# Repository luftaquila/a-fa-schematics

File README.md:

# E-Formula 전기시스템 파트 회로도 / PCB / 배선

상위 프로젝트: [luftaquila/a-fa-landing](https://github.com/luftaquila/a-fa-landing)

* 회로도  
    * *EV.kicad_pro*  
       * KiCAD 6.0 프로젝트  
       * 메인 회로도입니다. 추상적으로 차량의 모든 고전압/저전압 전기 계통이 표현되어 있습니다. 메인 회로도 하위의 계층 회로도는 개별 구성 요소를 추상화합니다. 계층 회로도 중 `/PCB` 폴더 하위의 파일들은 실제 PCB의 회로도입니다.

* PCB  
    * */PCB/\*.kicad_pcb*  
       * KiCAD 6.0 PCB 아트워크  
       * 각 PCB 폴더는 하나의 독립적인 KiCAD 프로젝트입니다. 메인 회로도인 `EV.kicad_sch` 파일이 계층 회로 구성을 통해 각 PCB 폴더의 `*.kicad_sch` 파일을 가리키는 방식으로 서로 연결되어 있습니다.

* 배선  
    * *wirings*
       * 차량의 모든 외부 배선을 표현하는 [WireViz](https://github.com/formatc1702/WireViz) 배선 체계도입니다.

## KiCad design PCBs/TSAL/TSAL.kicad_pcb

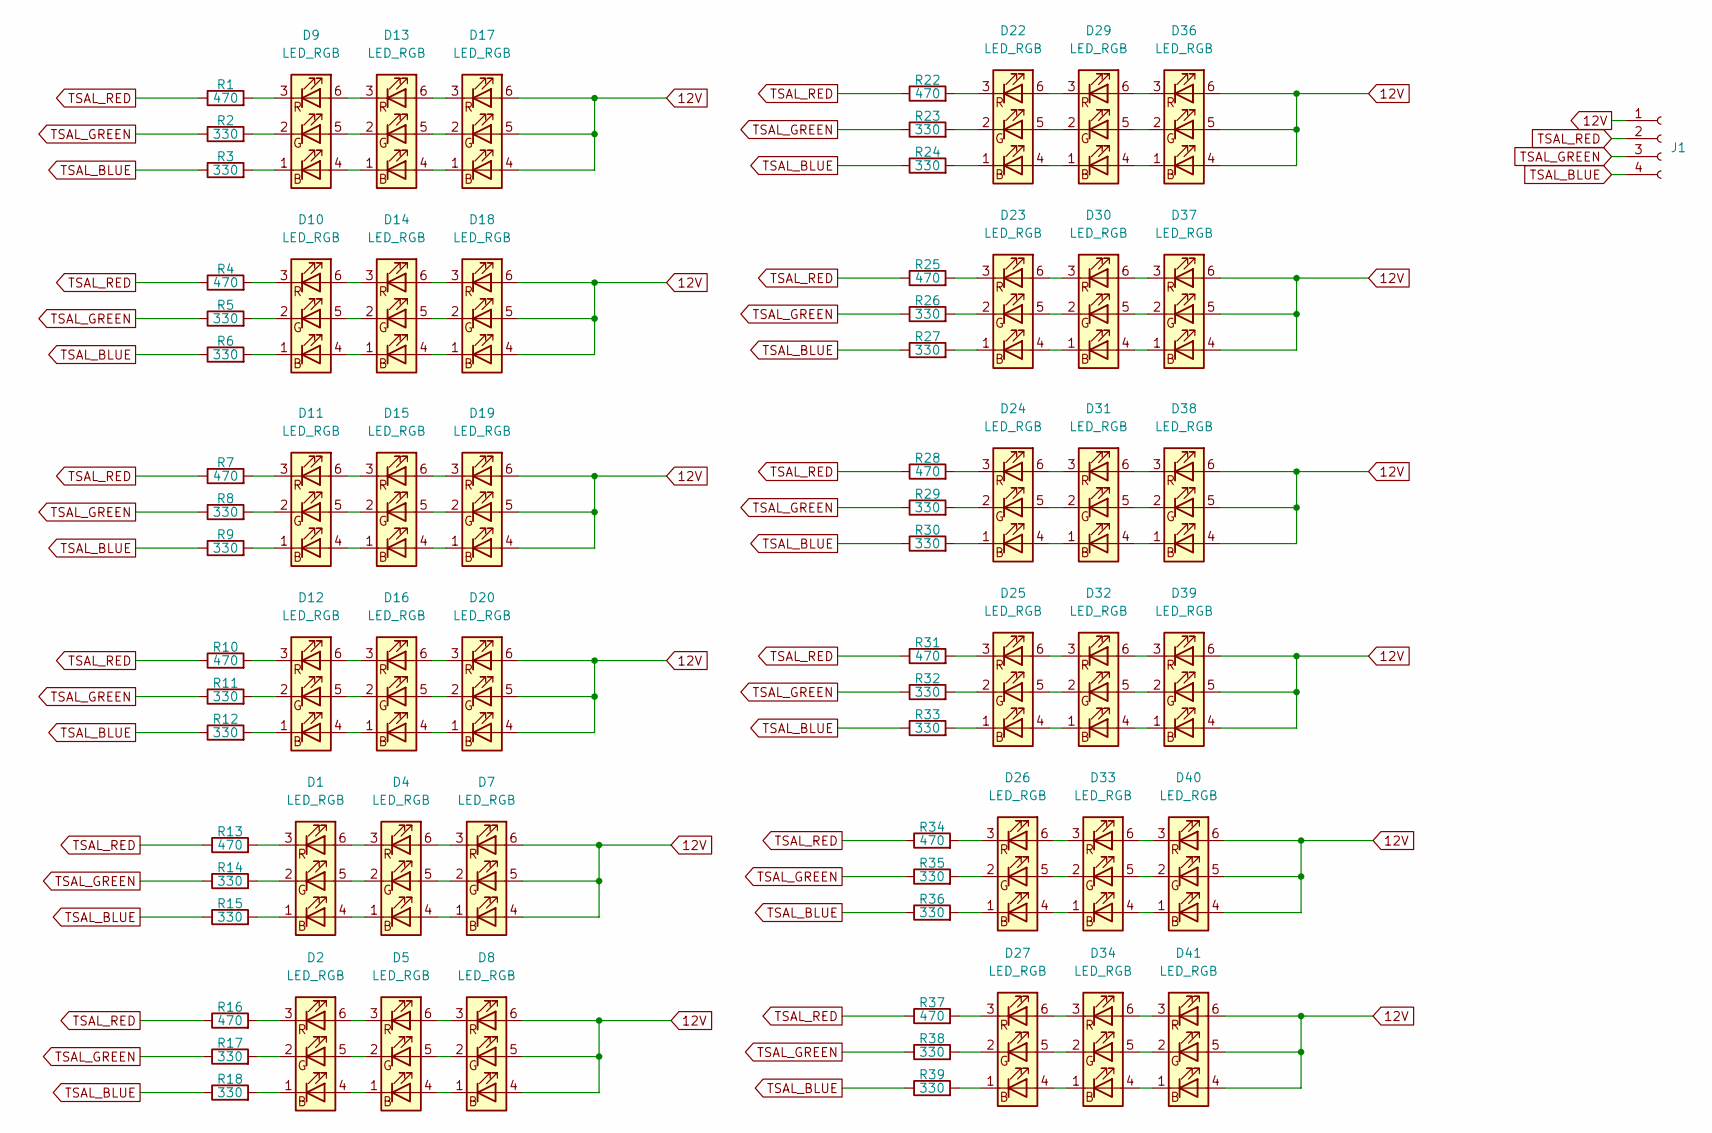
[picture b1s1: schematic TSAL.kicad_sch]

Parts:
D1, D2, D4, D5, D7, D8, D9, D10, D11, D12, D13, D14, D15, D16, D17, D18, D19, D20, D22, D23, D24, D25, D26, D27, D29, D30, D31, D32, D33, D34, D36, D37, D38, D39, D40, D41: LED_RGB; LED_RGB_5050-6
J1: Conn_01x04_Female; PinHeader_1x04_P2.54mm_Vertical
R1, R4, R7, R10, R13, R16, R22, R25, R28, R31, R34, R37: 470; R_1206_3216Metric_Pad1.30x1.75mm_HandSolder
R2, R3, R5, R6, R8, R9, R11, R12, R14, R15, R17, R18, R23, R24, R26, R27, R29, R30, R32, R33, R35, R36, R38, R39: 330; R_1206_3216Metric_Pad1.30x1.75mm_HandSolder

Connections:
12V: D7.4 (BA), D7.5 (GA), D7.6 (RA), D8.4 (BA), D8.5 (GA), D8.6 (RA), D17.4 (BA), D17.5 (GA), D17.6 (RA), D18.4 (BA), D18.5 (GA), D18.6 (RA), D19.4 (BA), D19.5 (GA), D19.6 (RA), D20.4 (BA), D20.5 (GA), D20.6 (RA), D36.4 (BA), D36.5 (GA), D36.6 (RA), D37.4 (BA), D37.5 (GA), D37.6 (RA), D38.4 (BA), D38.5 (GA), D38.6 (RA), D39.4 (BA), D39.5 (GA), D39.6 (RA), D40.4 (BA), D40.5 (GA), D40.6 (RA), D41.4 (BA), D41.5 (GA), D41.6 (RA), J1.1
unnamed: D1.1 (BK), R15.2
unnamed: D1.2 (GK), R14.2
unnamed: D1.3 (RK), R13.2
unnamed: D1.4 (BA), D4.1 (BK)
unnamed: D1.5 (GA), D4.2 (GK)
unnamed: D1.6 (RA), D4.3 (RK)
unnamed: D2.1 (BK), R18.2
unnamed: D2.2 (GK), R17.2
unnamed: D2.3 (RK), R16.2
unnamed: D2.4 (BA), D5.1 (BK)
unnamed: D2.5 (GA), D5.2 (GK)
unnamed: D2.6 (RA), D5.3 (RK)
unnamed: D4.4 (BA), D7.1 (BK)
unnamed: D4.5 (GA), D7.2 (GK)
unnamed: D4.6 (RA), D7.3 (RK)
unnamed: D5.4 (BA), D8.1 (BK)
unnamed: D5.5 (GA), D8.2 (GK)
unnamed: D5.6 (RA), D8.3 (RK)
unnamed: D9.1 (BK), R3.2
unnamed: D9.2 (GK), R2.2
unnamed: D9.3 (RK), R1.2
unnamed: D10.1 (BK), R6.2
unnamed: D10.2 (GK), R5.2
unnamed: D10.3 (RK), R4.2
unnamed: D10.4 (BA), D14.1 (BK)
unnamed: D10.5 (GA), D14.2 (GK)
unnamed: D10.6 (RA), D14.3 (RK)
unnamed: D11.1 (BK), R9.2
unnamed: D11.2 (GK), R8.2
unnamed: D11.3 (RK), R7.2
unnamed: D11.4 (BA), D15.1 (BK)
unnamed: D11.5 (GA), D15.2 (GK)
unnamed: D11.6 (RA), D15.3 (RK)
unnamed: D12.1 (BK), R12.2
unnamed: D12.2 (GK), R11.2
unnamed: D12.3 (RK), R10.2
unnamed: D12.4 (BA), D16.1 (BK)
unnamed: D12.5 (GA), D16.2 (GK)
unnamed: D12.6 (RA), D16.3 (RK)
unnamed: D9.4 (BA), D13.1 (BK)
unnamed: D9.5 (GA), D13.2 (GK)
unnamed: D9.6 (RA), D13.3 (RK)
unnamed: D13.4 (BA), D17.1 (BK)
unnamed: D13.5 (GA), D17.2 (GK)
unnamed: D13.6 (RA), D17.3 (RK)
unnamed: D14.4 (BA), D18.1 (BK)
unnamed: D14.5 (GA), D18.2 (GK)
unnamed: D14.6 (RA), D18.3 (RK)
unnamed: D15.4 (BA), D19.1 (BK)
unnamed: D15.5 (GA), D19.2 (GK)
unnamed: D15.6 (RA), D19.3 (RK)
unnamed: D16.4 (BA), D20.1 (BK)
unnamed: D16.5 (GA), D20.2 (GK)
unnamed: D16.6 (RA), D20.3 (RK)
unnamed: D22.1 (BK), R24.2
unnamed: D22.2 (GK), R23.2
unnamed: D22.3 (RK), R22.2
unnamed: D22.4 (BA), D29.1 (BK)
unnamed: D22.5 (GA), D29.2 (GK)
unnamed: D22.6 (RA), D29.3 (RK)
unnamed: D23.1 (BK), R27.2
unnamed: D23.2 (GK), R26.2
unnamed: D23.3 (RK), R25.2
unnamed: D23.4 (BA), D30.1 (BK)
unnamed: D23.5 (GA), D30.2 (GK)
unnamed: D23.6 (RA), D30.3 (RK)
unnamed: D24.1 (BK), R30.2
unnamed: D24.2 (GK), R29.2
unnamed: D24.3 (RK), R28.2
unnamed: D24.4 (BA), D31.1 (BK)
unnamed: D24.5 (GA), D31.2 (GK)
unnamed: D24.6 (RA), D31.3 (RK)
unnamed: D25.1 (BK), R33.2
unnamed: D25.2 (GK), R32.2
unnamed: D25.3 (RK), R31.2
unnamed: D25.4 (BA), D32.1 (BK)
unnamed: D25.5 (GA), D32.2 (GK)
unnamed: D25.6 (RA), D32.3 (RK)
unnamed: D26.1 (BK), R36.2
unnamed: D26.2 (GK), R35.2
unnamed: D26.3 (RK), R34.2
unnamed: D26.4 (BA), D33.1 (BK)
unnamed: D26.5 (GA), D33.2 (GK)
unnamed: D26.6 (RA), D33.3 (RK)
unnamed: D27.1 (BK), R39.2
unnamed: D27.2 (GK), R38.2
unnamed: D27.3 (RK), R37.2
unnamed: D27.4 (BA), D34.1 (BK)
unnamed: D27.5 (GA), D34.2 (GK)
unnamed: D27.6 (RA), D34.3 (RK)
unnamed: D29.4 (BA), D36.1 (BK)
unnamed: D29.5 (GA), D36.2 (GK)
unnamed: D29.6 (RA), D36.3 (RK)
unnamed: D30.4 (BA), D37.1 (BK)
unnamed: D30.5 (GA), D37.2 (GK)
unnamed: D30.6 (RA), D37.3 (RK)
unnamed: D31.4 (BA), D38.1 (BK)
unnamed: D31.5 (GA), D38.2 (GK)
unnamed: D31.6 (RA), D38.3 (RK)
unnamed: D32.4 (BA), D39.1 (BK)
unnamed: D32.5 (GA), D39.2 (GK)
unnamed: D32.6 (RA), D39.3 (RK)
unnamed: D33.4 (BA), D40.1 (BK)
unnamed: D33.5 (GA), D40.2 (GK)
unnamed: D33.6 (RA), D40.3 (RK)
unnamed: D34.4 (BA), D41.1 (BK)
unnamed: D34.5 (GA), D41.2 (GK)
unnamed: D34.6 (RA), D41.3 (RK)
TSAL_BLUE: J1.4, R3.1, R6.1, R9.1, R12.1, R15.1, R18.1, R24.1, R27.1, R30.1, R33.1, R36.1, R39.1
TSAL_GREEN: J1.3, R2.1, R5.1, R8.1, R11.1, R14.1, R17.1, R23.1, R26.1, R29.1, R32.1, R35.1, R38.1
TSAL_RED: J1.2, R1.1, R4.1, R7.1, R10.1, R13.1, R16.1, R22.1, R25.1, R28.1, R31.1, R34.1, R37.1

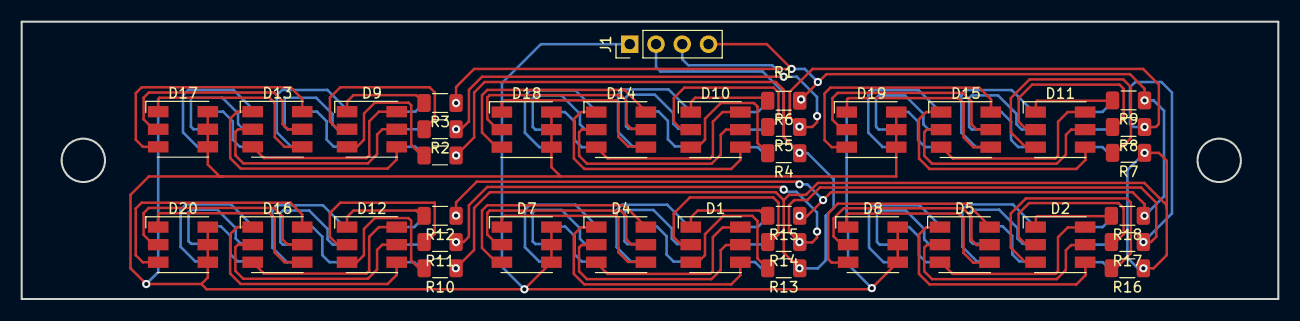
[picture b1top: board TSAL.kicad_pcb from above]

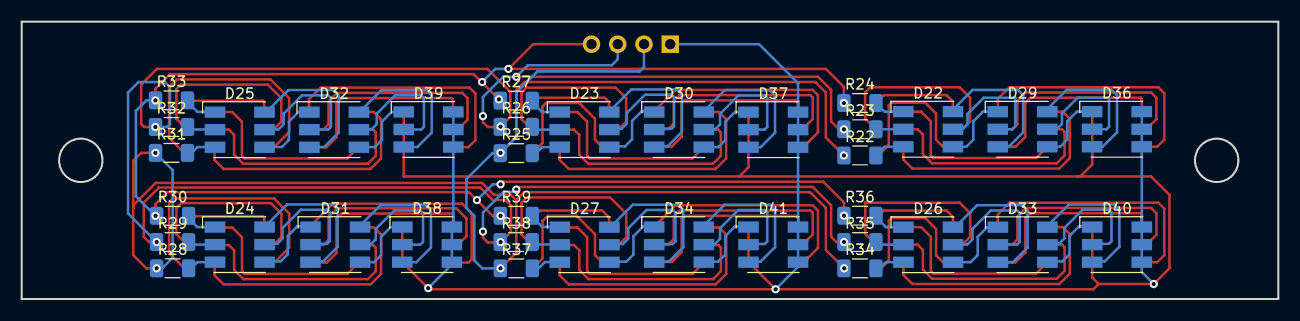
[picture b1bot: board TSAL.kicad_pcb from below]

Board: 2 copper layers, 121.7 x 26.9 mm, 73 parts (36 on the bottom side), 112 nets.

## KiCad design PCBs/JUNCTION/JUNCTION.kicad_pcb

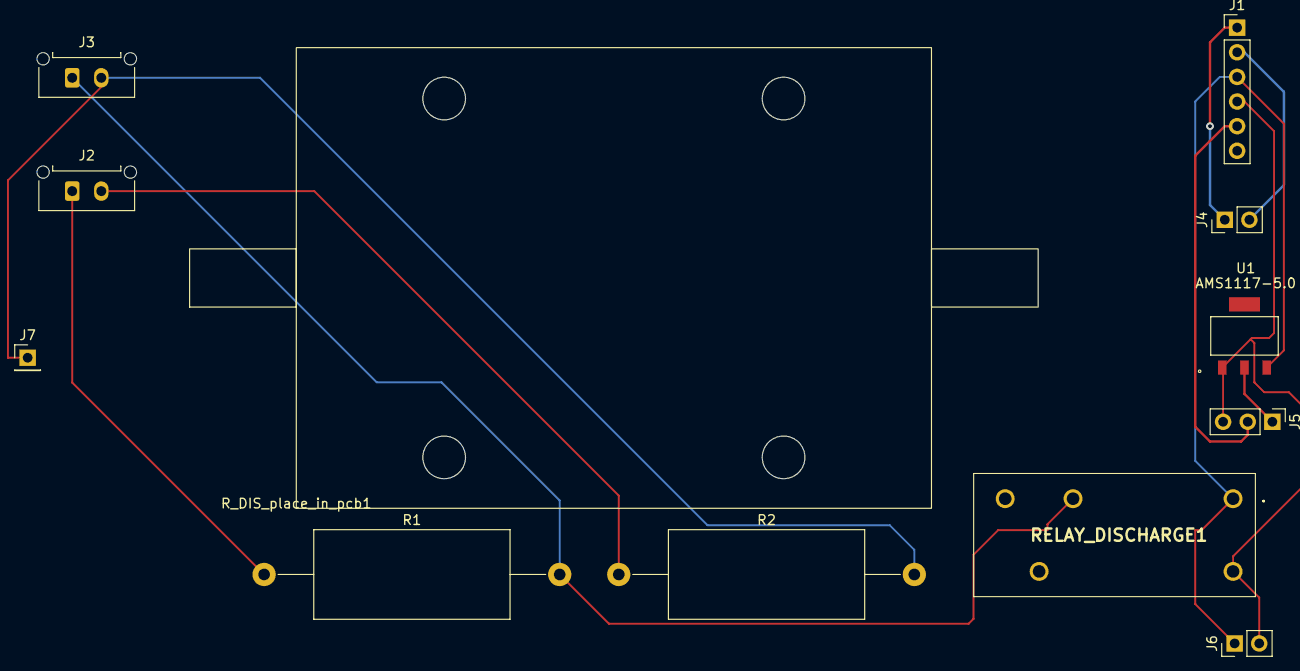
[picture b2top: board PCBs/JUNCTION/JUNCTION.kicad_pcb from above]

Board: 2 copper layers, 12 parts (0 on the bottom side), 10 nets.

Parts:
J1: JUNC; PinHeader_1x06_P2.54mm_Vertical
J2: TSMP; Molex_Micro-Fit_3.0_43650-0215_1x02_P3.00mm_Vertical
J3: HV; Molex_Micro-Fit_3.0_43650-0215_1x02_P3.00mm_Vertical
J4: HVD_IN; PinHeader_1x02_P2.54mm_Vertical
J5: HALL; PinHeader_1x03_P2.54mm_Vertical
J6: ENERGYMETER; PinHeader_1x02_P2.54mm_Vertical
J7: R_DISCHARGE; PinHeader_1x01_P2.54mm_Vertical
R1, R2: 10k; R_Axial_DIN0922_L20.0mm_D9.0mm_P30.48mm_Horizontal
RELAY_DISCHARGE1: G2RL-1_12DC; G2RL112DC
R_DIS_place_in_pcb1: 1k; HSC100
U1: AMS1117-5.0

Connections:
5V_{HALL}: J5.1, U1.2 (VO)
HALL_SIG: J1.5, J5.2
HV+: J3.1, R1.2, RELAY_DISCHARGE1.2 (NC)
HV-: J3.2, J7.1, R2.2
HVD1: J1.1, J4.1
HVD2: J1.2, J4.2
LV_{JNC}+: J1.3, J6.1, RELAY_DISCHARGE1.1 (COIL_1), U1.3 (VI)
LV_{JNC}-: J1.4, J5.3, J6.2, RELAY_DISCHARGE1.5 (COIL_2), U1.1 (GND)
TSMP+: J2.1, R1.1
TSMP-: J2.2, R2.1

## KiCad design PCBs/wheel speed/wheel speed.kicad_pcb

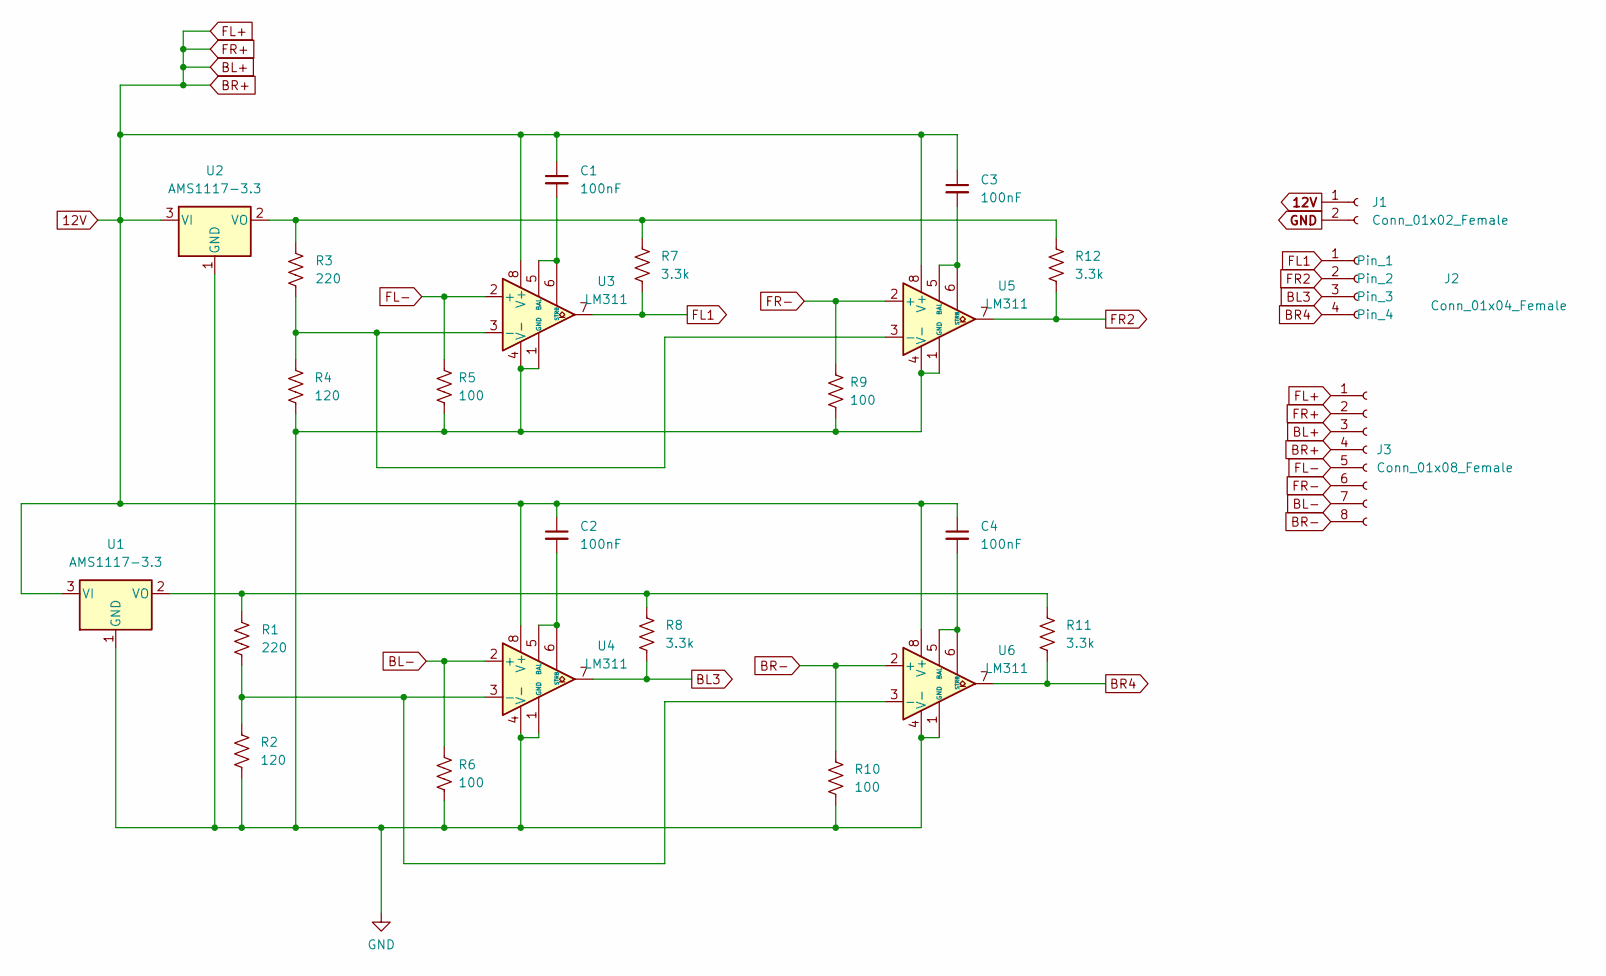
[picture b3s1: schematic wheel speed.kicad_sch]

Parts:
C1, C2, C3, C4: 100nF; C_Disc_D5.0mm_W2.5mm_P2.50mm
J1: Conn_01x02_Female; PinHeader_1x02_P2.54mm_Vertical
J2: Conn_01x04_Female; PinHeader_1x04_P2.54mm_Vertical
J3: Conn_01x08_Female; PinHeader_1x08_P2.54mm_Vertical
R1, R3: 220; R_Axial_DIN0207_L6.3mm_D2.5mm_P10.16mm_Horizontal
R2, R4: 120; R_Axial_DIN0207_L6.3mm_D2.5mm_P10.16mm_Horizontal
R5, R6, R9, R10: 100; R_Axial_DIN0207_L6.3mm_D2.5mm_P10.16mm_Horizontal
R7, R8, R11, R12: 3.3k; R_Axial_DIN0207_L6.3mm_D2.5mm_P10.16mm_Horizontal
U1, U2: AMS1117-3.3; AMS1117-5.0
U3, U4, U5, U6: LM311; LM311P

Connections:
12V: C1.1, C2.1, C3.1, C4.1, J1.1, J3.1, J3.2, J3.3, J3.4, U1.3 (VI), U2.3 (VI), U3.8 (V+), U4.8 (V+), U5.8 (V+), U6.8 (V+)
BL3: J2.3, R8.1, U4.7
BL-: J3.7, R6.2, U4.2 (+)
BR4: J2.4, R11.1, U6.7
BR-: J3.8, R10.2, U6.2 (+)
FL1: J2.1, R7.1, U3.7
FL-: J3.5, R5.2, U3.2 (+)
FR2: J2.2, R12.1, U5.7
FR-: J3.6, R9.2, U5.2 (+)
GND: J1.2, R2.1, R4.1, R5.1, R6.1, R9.1, R10.1, U1.1 (GND), U2.1 (GND), U3.1 (GND), U3.4 (V-), U4.1 (GND), U4.4 (V-), U5.1 (GND), U5.4 (V-), U6.1 (GND), U6.4 (V-)
unnamed: C1.2, U3.5 (BAL), U3.6 (STRB)
unnamed: C2.2, U4.5 (BAL), U4.6 (STRB)
unnamed: C3.2, U5.5 (BAL), U5.6 (STRB)
unnamed: C4.2, U6.5 (BAL), U6.6 (STRB)
unnamed: R1.1, R8.2, R11.2, U1.2 (VO)
unnamed: R1.2, R2.2, U4.3 (-), U6.3 (-)
unnamed: R3.2, R4.2, U3.3 (-), U5.3 (-)
unnamed: R3.1, R7.2, R12.2, U2.2 (VO)

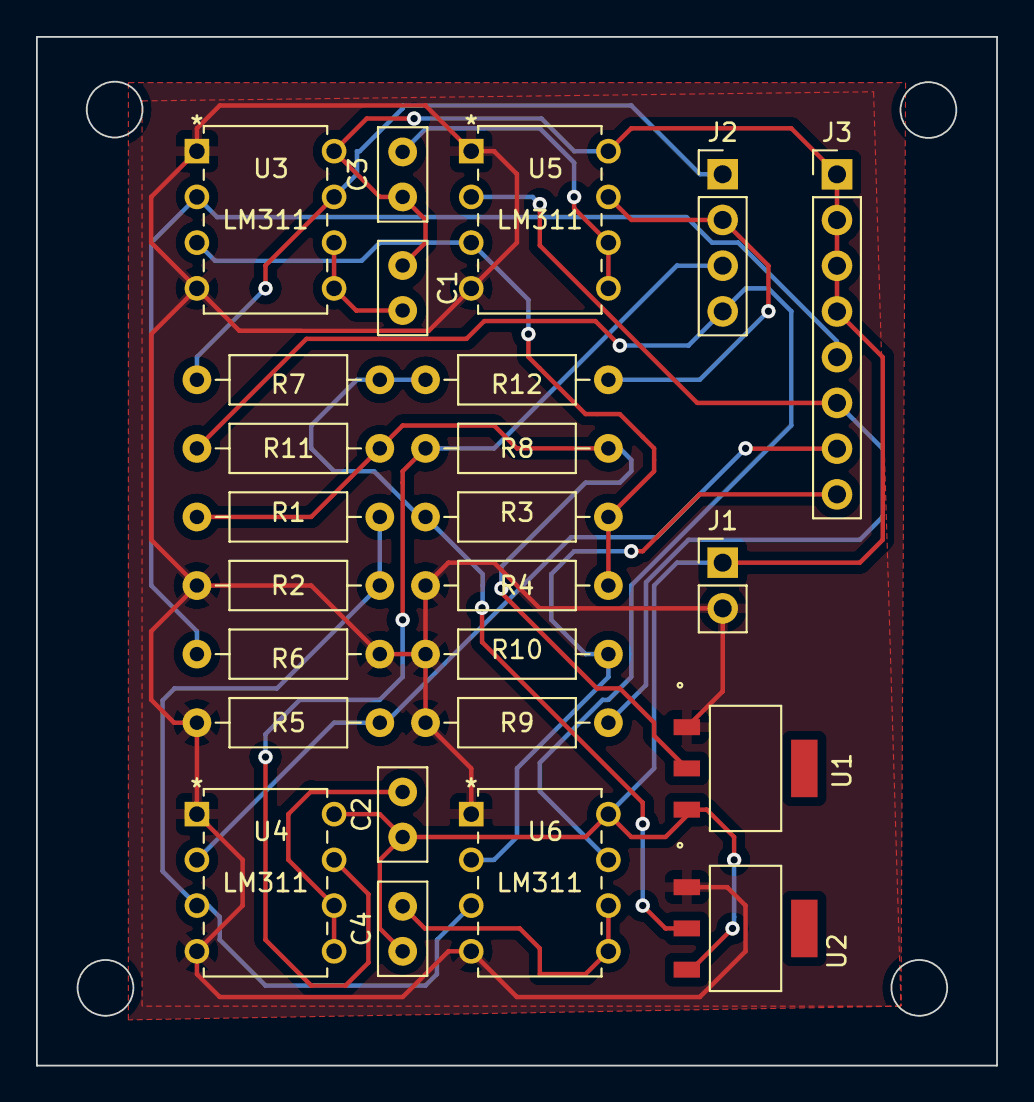
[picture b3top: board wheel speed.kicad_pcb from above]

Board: 2 copper layers, 53.3 x 57.1 mm, 25 parts (0 on the bottom side), 18 nets.

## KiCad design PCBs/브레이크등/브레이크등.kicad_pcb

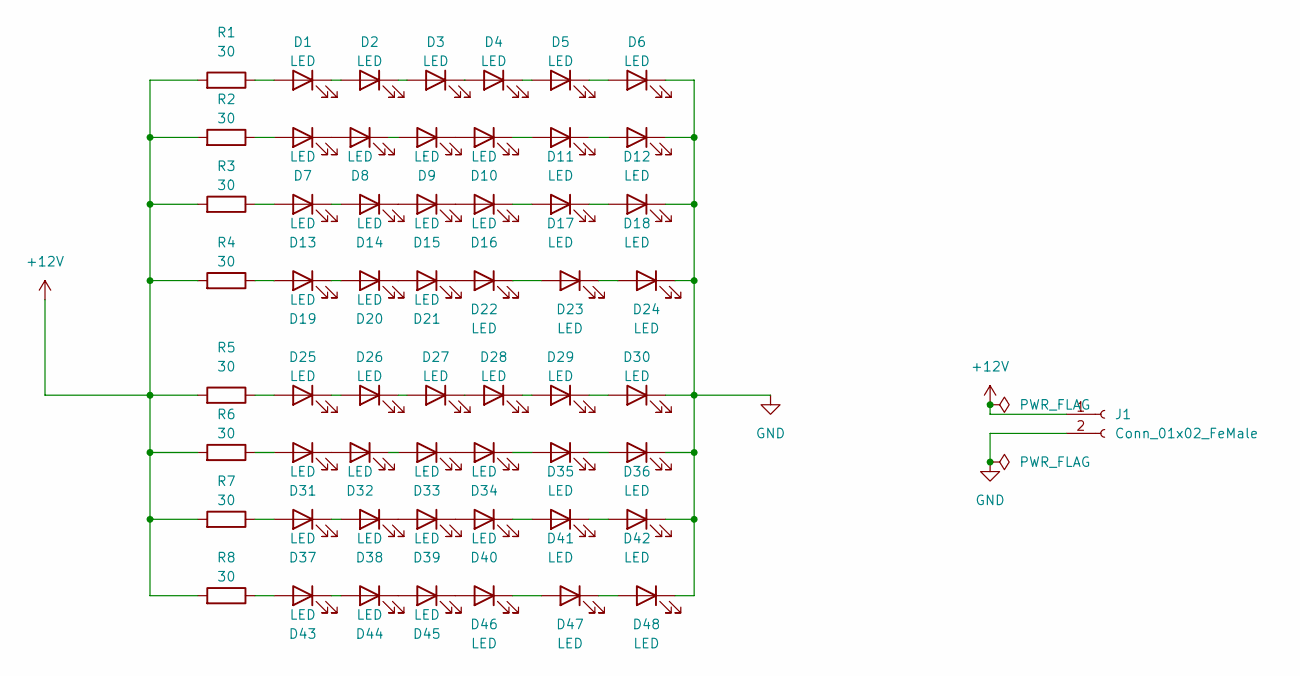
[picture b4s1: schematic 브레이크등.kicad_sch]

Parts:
D1, D2, D3, D4, D5, D6, D7, D8, D9, D10, D11, D12, D13, D14, D15, D16, D17, D18, D19, D20, D21, D22, D23, D24, D25, D26, D27, D28, D29, D30, D31, D32, D33, D34, D35, D36, D37, D38, D39, D40, D41, D42, D43, D44, D45, D46, D47, D48: LED; LED_RGB_5050-6_copy
J1: Conn_01x02_FeMale; Molex_Mini-Fit_Jr_5569-02A1_2x01_P4.20mm_Horizontal
R1, R2, R3, R4, R5, R6, R7, R8: 30; R_Axial_DIN0207_L6.3mm_D2.5mm_P10.16mm_Horizontal

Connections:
+12V: J1.1, R1.2, R2.2, R3.2, R4.2, R5.2, R6.2, R7.2, R8.2
GND: D6.1 (K), D12.1 (K), D18.1 (K), D24.1 (K), D30.1 (K), D36.1 (K), D42.1 (K), D48.1 (K), J1.2
unnamed: D1.1 (K), D2.2 (A)
unnamed: D1.2 (A), R1.1
unnamed: D2.1 (K), D3.2 (A)
unnamed: D3.1 (K), D4.2 (A)
unnamed: D4.1 (K), D5.2 (A)
unnamed: D5.1 (K), D6.2 (A)
unnamed: D7.1 (K), D8.2 (A)
unnamed: D7.2 (A), R2.1
unnamed: D8.1 (K), D9.2 (A)
unnamed: D10.1 (K), D11.2 (A)
unnamed: D9.1 (K), D10.2 (A)
unnamed: D11.1 (K), D12.2 (A)
unnamed: D13.1 (K), D14.2 (A)
unnamed: D13.2 (A), R3.1
unnamed: D14.1 (K), D15.2 (A)
unnamed: D15.1 (K), D16.2 (A)
unnamed: D16.1 (K), D17.2 (A)
unnamed: D17.1 (K), D18.2 (A)
unnamed: D19.1 (K), D20.2 (A)
unnamed: D19.2 (A), R4.1
unnamed: D20.1 (K), D21.2 (A)
unnamed: D21.1 (K), D22.2 (A)
unnamed: D22.1 (K), D23.2 (A)
unnamed: D23.1 (K), D24.2 (A)
unnamed: D25.1 (K), D26.2 (A)
unnamed: D25.2 (A), R5.1
unnamed: D26.1 (K), D27.2 (A)
unnamed: D27.1 (K), D28.2 (A)
unnamed: D28.1 (K), D29.2 (A)
unnamed: D29.1 (K), D30.2 (A)
unnamed: D31.1 (K), D32.2 (A)
unnamed: D31.2 (A), R6.1
unnamed: D32.1 (K), D33.2 (A)
unnamed: D33.1 (K), D34.2 (A)
unnamed: D34.1 (K), D35.2 (A)
unnamed: D35.1 (K), D36.2 (A)
unnamed: D37.1 (K), D38.2 (A)
unnamed: D37.2 (A), R7.1
unnamed: D38.1 (K), D39.2 (A)
unnamed: D39.1 (K), D40.2 (A)
unnamed: D40.1 (K), D41.2 (A)
unnamed: D41.1 (K), D42.2 (A)
unnamed: D43.1 (K), D44.2 (A)
unnamed: D43.2 (A), R8.1
unnamed: D44.1 (K), D45.2 (A)
unnamed: D45.1 (K), D46.2 (A)
unnamed: D46.1 (K), D47.2 (A)
unnamed: D47.1 (K), D48.2 (A)

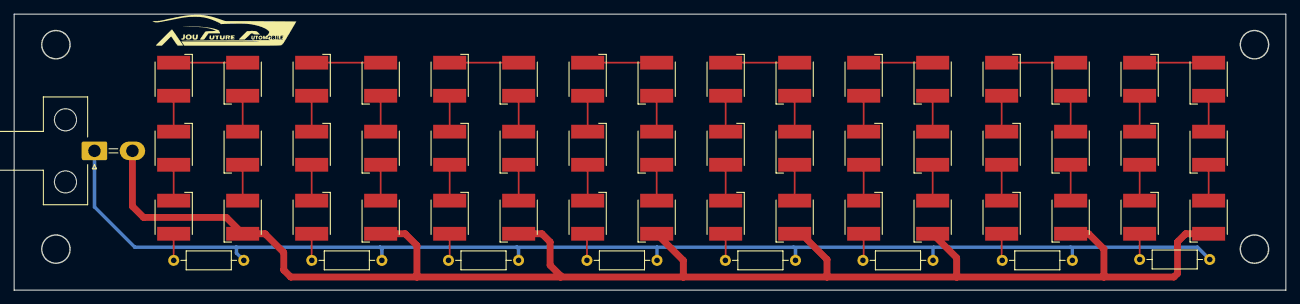
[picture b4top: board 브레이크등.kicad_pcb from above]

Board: 2 copper layers, 184.3 x 40.0 mm, 58 parts (0 on the bottom side), 50 nets.

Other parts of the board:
A-FA: bf078263-bd62-418a-b936-95124366838e

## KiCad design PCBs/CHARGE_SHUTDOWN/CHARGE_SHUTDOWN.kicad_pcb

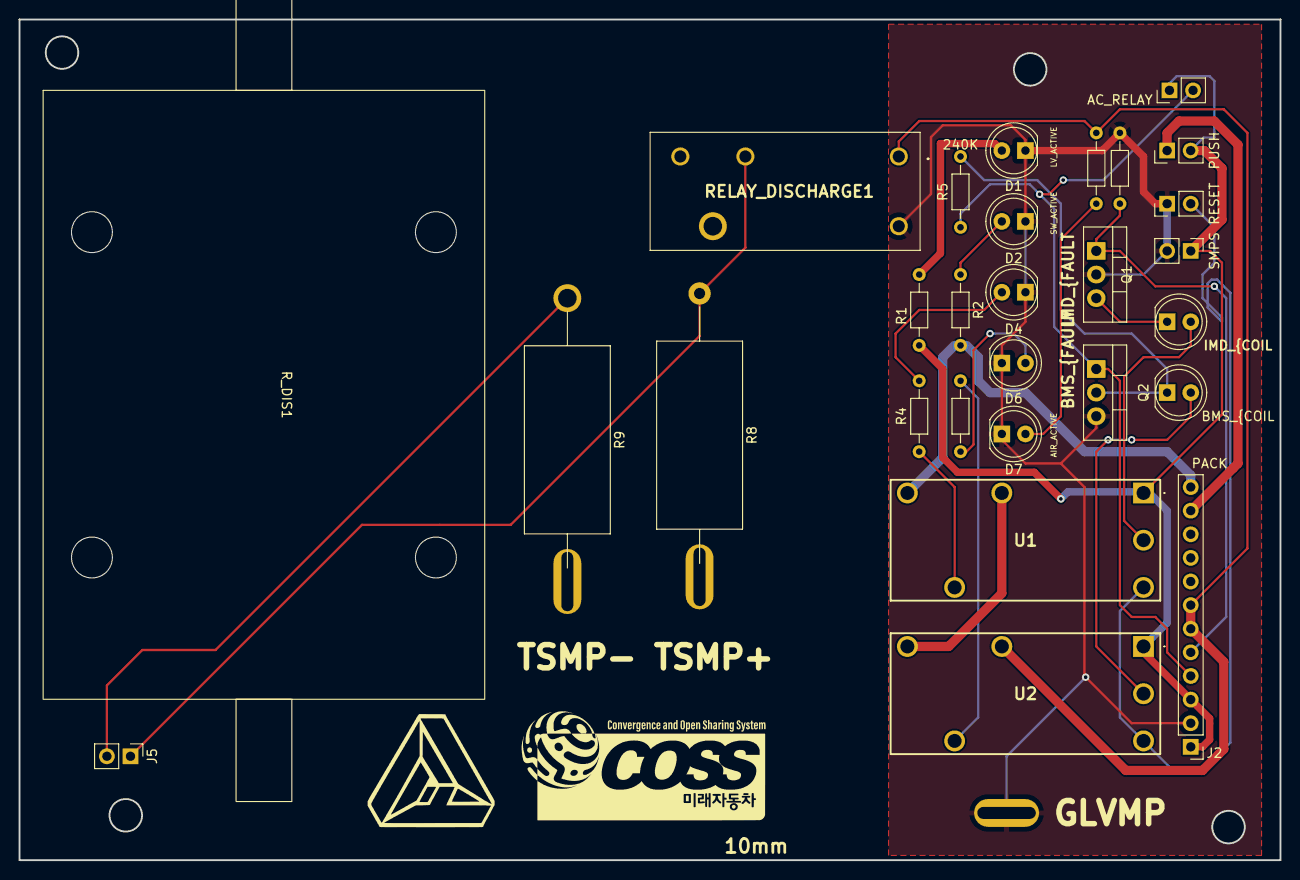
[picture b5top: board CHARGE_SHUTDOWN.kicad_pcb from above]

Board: 2 copper layers, 135.6 x 90.4 mm, 29 parts (0 on the bottom side), 22 nets.

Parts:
AC_RELAY: AC_RELAY; PinHeader_1x02_P2.54mm_Vertical
D1: LV_ACTIVE; LED_D5.0mm
D2: SW_ACTIVE; LED_D5.0mm
D3: IMD_{COIL; LED_D5.0mm
D4: IMD_{FAULT; LED_D5.0mm
D5: BMS_{COIL; LED_D5.0mm
D6: BMS_{FAULT; LED_D5.0mm
D7: AIR_ACTIVE; LED_D5.0mm
J2: PACK; PinHeader_1x12_P2.54mm_Vertical
J5: HV; PinHeader_1x02_P2.54mm_Vertical
J7: Conn_01x01_Female; Banana_Jack_1Pin
PUSH: PUSH_ROTATE; PinHeader_1x02_P2.54mm_Vertical
Q1: IRF9540N; TO-220-3_Vertical
Q2: IRF740; TO-220-3_Vertical
R1, R2, R3, R4, R6, R7: 10k; R_Axial_DIN0204_L3.6mm_D1.6mm_P7.62mm_Horizontal
R5: 240K; R_Axial_DIN0204_L3.6mm_D1.6mm_P7.62mm_Horizontal
R8, R9: 10K; R_Axial_DIN0922_L20.0mm_D9.0mm_P30.48mm_Horizontal
RELAY_DISCHARGE1: G2RL-1_12DC; G2RL112DC
RESET: RESET; PinHeader_1x02_P2.54mm_Vertical
R_DIS1: 1k; HSC100
SMPS: SMPS; PinHeader_1x02_P2.54mm_Vertical
U1, U2: ADJ14012; ADJ14024

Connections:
AIR+_ACTIVE: J2.6, J2.7, R7.2, RELAY_DISCHARGE1.1 (COIL_1), U2.2 (Out)
CHARGER_SAFETY: AC_RELAY.2, J2.4, Q2.1 (G), R5.1
CHARGE_POWER: AC_RELAY.1, J2.1, J2.3, PUSH.2, R1.2, SMPS.1, U1.1 (V), U2.1 (V)
GND_BOX: D1.1 (K), D2.1 (K), D4.1 (K), D6.1 (K), D7.1 (K), J2.2, J7.1, Q1.2 (D), Q2.3 (S), R3.1, RELAY_DISCHARGE1.5 (COIL_2), RESET.1, SMPS.2
IMD_FAULT: J2.5, Q1.1 (G), R3.2
INTERLOCK_{1}: J2.11, PUSH.1
INTERLOCK_{2}: J2.12, R2.2, U1.4 (12V)
unnamed: D1.2 (A), R1.1
unnamed: D2.2 (A), R2.1
unnamed: D3.1 (K), Q1.3 (S)
unnamed: D3.2 (A), U1.9 (D)
unnamed: D4.2 (A), R4.2
unnamed: D5.1 (K), Q2.2 (D), R5.2
unnamed: D5.2 (A), U2.9 (D)
unnamed: D6.2 (A), R6.2
unnamed: D7.2 (A), R7.1
unnamed: J5.1, R8.1, RELAY_DISCHARGE1.2 (NC)
unnamed: J5.2, R9.1
unnamed: R4.1, U1.6 (N)
unnamed: R6.1, U2.6 (N)
unnamed: U1.2 (Out), U2.4 (12V)
Reset_Button: RESET.2, U1.8 (L), U2.8 (L)

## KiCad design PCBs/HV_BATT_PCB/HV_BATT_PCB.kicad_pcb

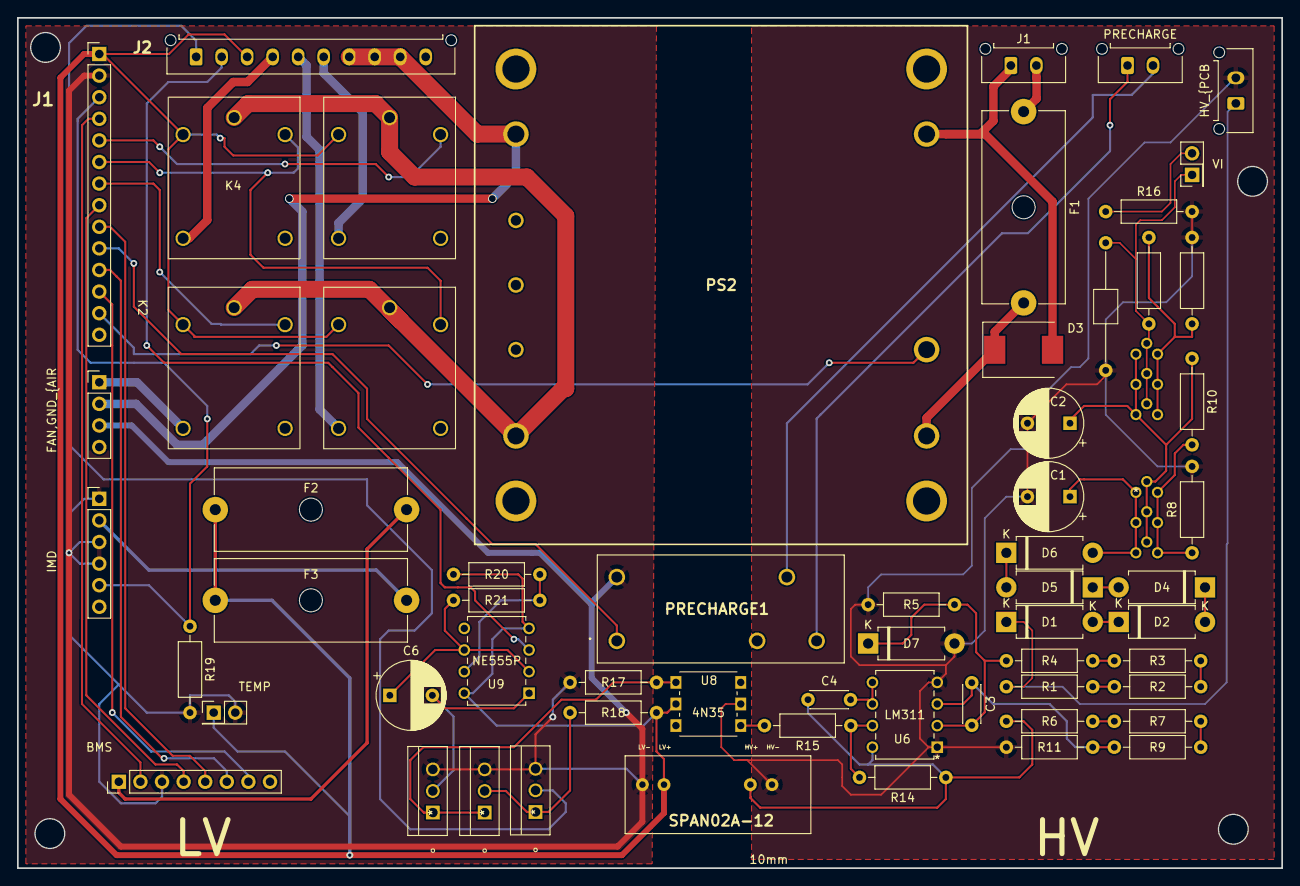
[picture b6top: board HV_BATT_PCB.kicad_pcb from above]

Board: 2 copper layers, 148.7 x 100.0 mm, 66 parts (0 on the bottom side), 56 nets.

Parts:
BMS: Conn_01x08_Male; PinHeader_1x08_P2.54mm_Vertical
C1, C2: 2.2uF; CP_Radial_D8.0mm_P5.00mm
C3: 1nF; C_Disc_D4.3mm_W1.9mm_P5.00mm
C4: 1uF; C_Disc_D4.3mm_W1.9mm_P5.00mm
C5: 1uF; C_Axial_L3.8mm_D2.6mm_P15.00mm_Horizontal
C6: 1uF; CP_Radial_D8.0mm_P5.00mm
D1, D2, D4, D5, D6, D7: 1N5349; D_DO-15_P10.16mm_Horizontal
D3: TVS; D_SMC
F1: SMCJ440A; Fuseholder_Cylinder-5x20mm_Schurter_0031_8201_Horizontal_Op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
F2: 1A Fuse; Fuseholder_Cylinder-5x20mm_Schurter_0031_8201_Horizontal_Op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
F3: 3A Fuse; Fuseholder_Cylinder-5x20mm_Schurter_0031_8201_Horizontal_Op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
FAN,GND_{AIR: Conn_01x04_Male; PinHeader_1x04_P2.54mm_Vertical
HV_{PCB: HV_{PCB; Molex_Micro-Fit_3.0_43650-0215_1x02_P3.00mm_Vertical
IMD: Conn_01x06_Male; PinHeader_1x06_P2.54mm_Vertical
J1: Conn_01x02_Male; Molex_Micro-Fit_3.0_43650-0215_1x02_P3.00mm_Vertical
J1#2: Conn_01x14_Male; PinHeader_1x14_P2.54mm_Vertical
J2: Conn_01x10_Male; Molex_Micro-Fit_3.0_43650-1015_1x10_P3.00mm_Vertical
K1: PUMP; HR702
K2: FAN_R; HR702
K3: FAN_L; HR702
K4: LV_BATT_FAN; HR702
PRECHARGE: Conn_01x02_Male; Molex_Micro-Fit_3.0_43650-0215_1x02_P3.00mm_Vertical
PRECHARGE1: G2RL-1_12DC; G2RL112DC
PS1: SPAN02A-12; SPAN02A12
PS2: QHL300300S12; QHL300300S28
Q1, Q2, Q3: IRF640; IRF640NPBF
R1, R2, R3, R4, R6, R7, R9, R11: 4.7M; R_Axial_DIN0207_L6.3mm_D2.5mm_P10.16mm_Horizontal
R5: 1M; R_Axial_DIN0207_L6.3mm_D2.5mm_P10.16mm_Horizontal
R8: 390k; R_Axial_DIN0207_L6.3mm_D2.5mm_P10.16mm_Horizontal
R10: 4.7k; R_Axial_DIN0207_L6.3mm_D2.5mm_P10.16mm_Horizontal
R12: 18k; R_Axial_DIN0207_L6.3mm_D2.5mm_P10.16mm_Horizontal
R13: 12k; R_Axial_DIN0207_L6.3mm_D2.5mm_P10.16mm_Horizontal
R14, R18: 10k; R_Axial_DIN0207_L6.3mm_D2.5mm_P10.16mm_Horizontal
R15, R19: 2k2; R_Axial_DIN0207_L6.3mm_D2.5mm_P10.16mm_Horizontal
R16: 1k; R_Axial_DIN0207_L6.3mm_D2.5mm_P10.16mm_Horizontal
R17: 100k; R_Axial_DIN0207_L6.3mm_D2.5mm_P10.16mm_Horizontal
R20, R21: 240k; R_Axial_DIN0207_L6.3mm_D2.5mm_P10.16mm_Horizontal
TEMP: Conn_01x02_Male; PinHeader_2x01_P2.54mm_Vertical
U1, U2, U3, U4, U5, U7: LR8; LR8N3-G
U6: LM311; LM311P
U8: 4N35
U9: NE555P
VI1: Conn_01x02_Male; PinHeader_2x01_P2.54mm_Vertical

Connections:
BMS_FAULT: BMS.2, J1#2.4
CAN_H_{BMS: BMS.4, J1#2.8
CAN_L_{BMS: BMS.5, J1#2.9
CHARGER_SAFETY: BMS.7, J1#2.12
CHARGE_POWER: BMS.6, J1#2.11
GND_AIR: BMS.3, FAN,GND_{AIR.3, IMD.1, IMD.3, IMD.4, J1#2.2, PRECHARGE1.5 (COIL_2), PS1.1 (-VIN), Q1.3 (S), Q2.3 (S), Q3.3 (S), R17.1, R19.2, TEMP.2
HV_{PCB}+: D1.1 (K), HV_{PCB.1, R1.1
HV_{PCB}-: C1.2, C2.2, C5.2, D7.2 (A), HV_{PCB.2, PS1.7 (-VOUT), R5.2, R8.2, R11.2, R12.2, R16.2, U6.1 (GND), U6.4 (V-), U8.2
IMD_FAULT: IMD.5, J1#2.3, R19.1
LV_{BATT_FAN}+: FAN,GND_{AIR.1, K2.14
LV_{BATT_FAN}-: FAN,GND_{AIR.2, J2.7, J2.8, J2.9, PS2.4 (-VOUT)
LV_{BMS}+: BMS.1, F2.2
LV_{COOLING1}: K1.7, K2.7, K3.7, K4.7, PS2.8 (+VOUT)
LV_{FAN_L}+: J2.5, K3.14
LV_{FAN_R}+: J2.4, K4.14
LV_{IMD}+: F3.2, IMD.2
LV_{PACK}+: F2.1, F3.1, J1#2.1, J2.3, K1.2, K2.2, K3.2, K4.2, PS1.2 (+VIN), R18.1, R20.2, TEMP.1, U8.5, U9.4 (R), U9.8 (VCC)
LV_{PUMP}+: J2.6, K1.14
unnamed: C1.1, D6.2 (A), U1.1 (IN), U2.1 (IN), U3.1 (IN)
unnamed: C2.1, R10.1, U1.2 (OUT), U2.2 (OUT), U3.2 (OUT), U4.1 (IN), U5.1 (IN), U7.1 (IN)
unnamed: C3.1, R9.2, R11.1, U6.3 (-)
unnamed: C3.2, D7.1 (K), R4.2, R5.1, U6.2 (+)
unnamed: C4.1, PS1.6 (+VOUT), R6.1, R14.1, U6.8 (V+)
unnamed: C4.2, U6.5 (BAL), U6.6 (STRB)
unnamed: C6.1, R21.1, U9.2 (TR), U9.6 (THR)
unnamed: C6.2, Q3.2 (D), U9.1 (GND)
unnamed: D1.2 (A), D2.1 (K)
unnamed: D2.2 (A), D4.1 (K)
unnamed: D3.1 (A1), F1.2, PS2.1 (+VIN)
unnamed: D3.2 (A2), J1.1, PS2.3 (-VIN)
unnamed: D4.2 (A), D5.1 (K)
unnamed: D5.2 (A), D6.1 (K)
unnamed: F1.1, J1.2
unnamed: Q1.1 (G), Q2.2 (D), R18.2
unnamed: Q2.1 (G), Q3.1 (G), R17.2, U8.4
unnamed: R1.2, R2.1
unnamed: R2.2, R3.1
unnamed: R3.2, R4.1
unnamed: R6.2, R7.1
unnamed: R7.2, R9.1
unnamed: R8.1, R10.2, U1.3 (ADJ), U2.3 (ADJ), U3.3 (ADJ)
unnamed: R12.1, R13.2, U4.3 (ADJ), U5.3 (ADJ), U7.3 (ADJ)
unnamed: R14.2, R15.1, U6.7
unnamed: R15.2, U8.1
unnamed: R20.1, R21.2, U9.7 (DIS)
ON_{BATT_FAN}: J1#2.7, K2.6
ON_{COOLING: J1#2.13, PS2.2 (REMOTE_ON/OFF)
ON_{PUMP}: J1#2.5, K1.6
ON_{RAD_FAN}: J1#2.6, K3.6, K4.6
PRECHARGE_DRIVE: J1#2.10, PRECHARGE1.1 (COIL_1)
RELAY_PRECHARGE: PRECHARGE.1, PRECHARGE1.3 (NO)
R_PRECHARGE: PRECHARGE.2, PRECHARGE1.4 (COM)
TSAL_GREEN: J2.1, Q1.2 (D)
TSAL_RED: J2.2, U9.3 (Q)
VI_LED+: C5.1, R13.1, U4.2 (OUT), U5.2 (OUT), U7.2 (OUT), VI1.1
VI_LED-: R16.1, VI1.2

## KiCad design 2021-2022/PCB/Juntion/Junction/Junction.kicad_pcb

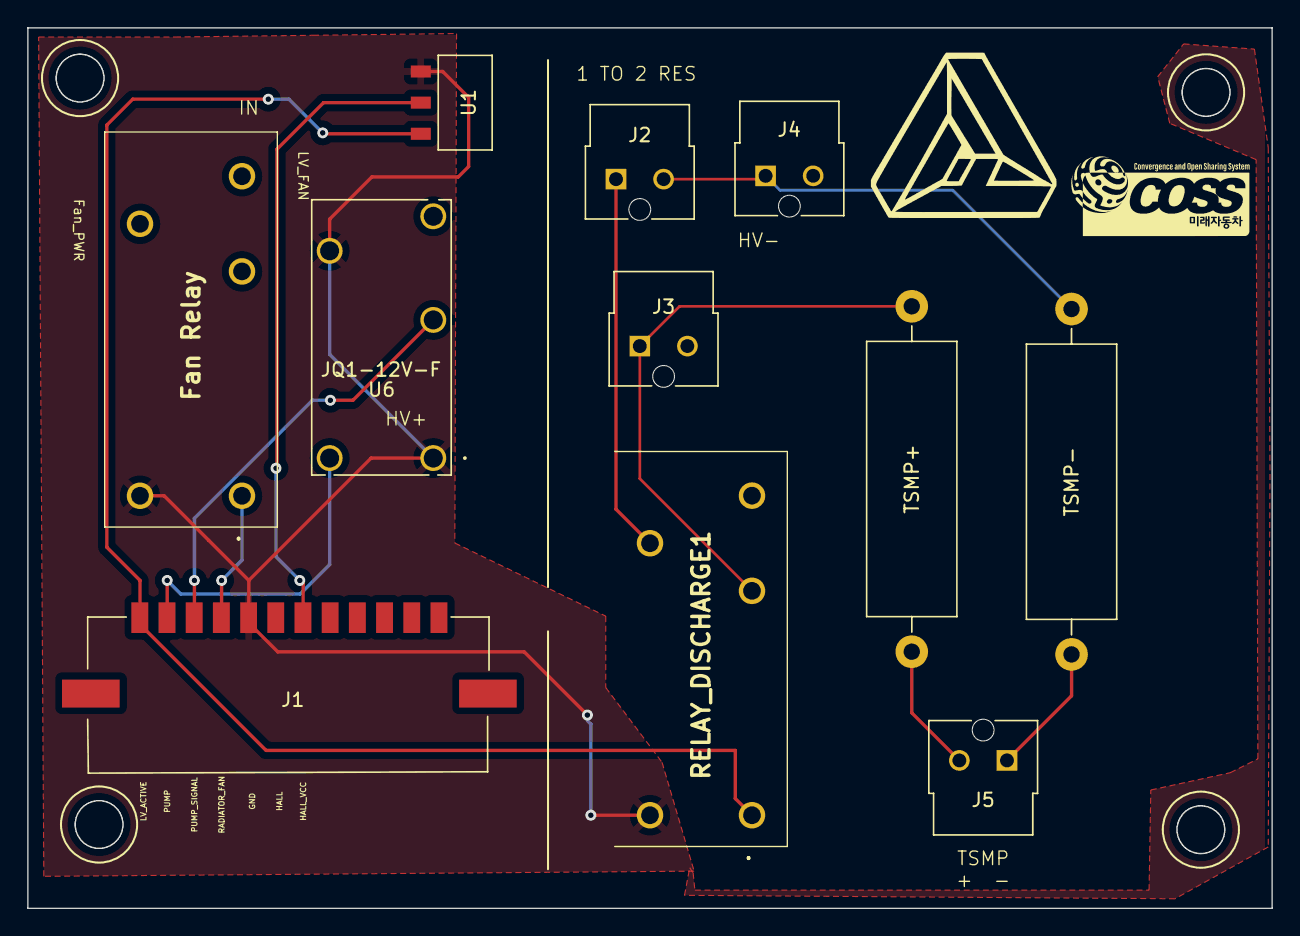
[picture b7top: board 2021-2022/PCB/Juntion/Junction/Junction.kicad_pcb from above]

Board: 2 copper layers, 91.5 x 64.8 mm, 11 parts (0 on the bottom side), 11 nets.

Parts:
Fan Relay: G2RL-1_12DC; G2RL112DC
J1: Conn_01x12_Female; 5600201220
J2, J3, J4, J5: Conn_01x02_Female; 1722861102
RELAY_DISCHARGE1: G2RL-1_12DC; G2RL112DC
TSMP+: R_Axial_Power_L20.0mm_W6.4mm_P25.40mm
TSMP-: R_Axial_Power_L20.0mm_W6.4mm_P25.40mm
U1: AMS1117-5.0
U6: JQ1-12V-F

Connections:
++: J5.2, TSMP+.1
--: J5.1, TSMP-.1
GND: Fan Relay.5 (COIL_2), J1.5, RELAY_DISCHARGE1.5 (COIL_2), U1.1 (GND), U6.1, U6.4
HV_IN+: J3.1, RELAY_DISCHARGE1.2 (NC), TSMP+.2
HV_IN-: J2.2, J4.1, TSMP-.2
LV_ACTIVE: J1.1, RELAY_DISCHARGE1.1 (COIL_1), U1.3 (VI)
unnamed: J2.1, RELAY_DISCHARGE1.4 (COM)
PUMP: J1.2, U6.5
PUMP_SIGNAL: J1.3, U6.2
RADIATOR_FAN: Fan Relay.1 (COIL_1), J1.4
chul: J1.7, U1.2 (VO)

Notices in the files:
parts and their libraries:
Copyright 2021 Accelerated Designs. All rights reserved.
